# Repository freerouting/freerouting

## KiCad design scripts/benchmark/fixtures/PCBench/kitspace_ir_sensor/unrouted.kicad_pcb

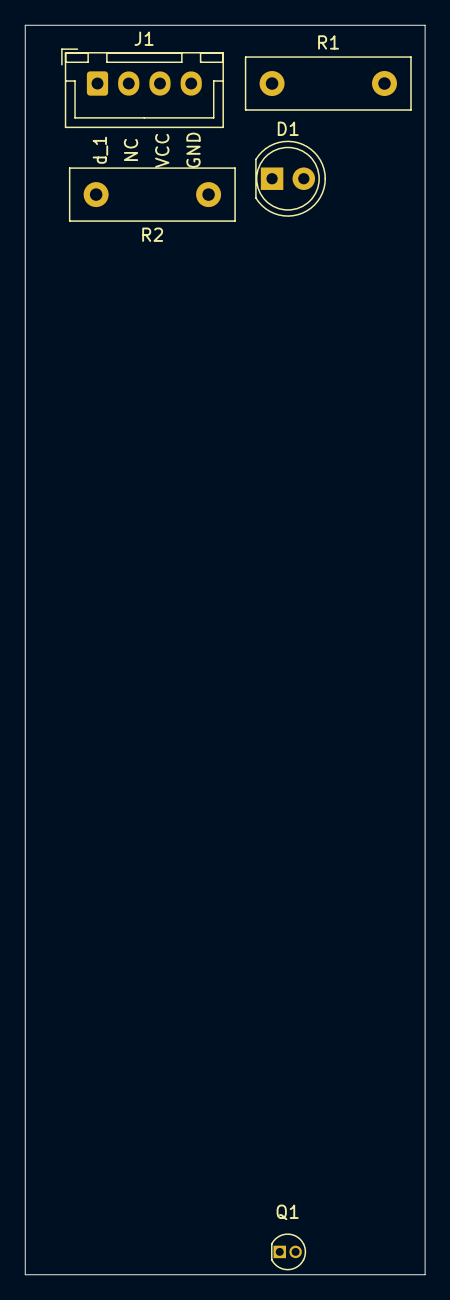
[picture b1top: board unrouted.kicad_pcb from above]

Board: 2 copper layers, 32.0 x 100.0 mm, 5 parts (0 on the bottom side), 4 nets, no tracks yet.

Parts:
D1: LED; LED_D5.0mm
J1: Conn_01x04; JST_XH_B4B-XH-A_1x04_P2.50mm_Vertical
Q1: Q_Photo_NPN; OP505A
R1: 47; R_Box_L13.0mm_W4.0mm_P9.00mm
R2: 10k; R_Box_L13.0mm_W4.0mm_P9.00mm

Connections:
+5V: J1.3, R1.1, R2.1
GND: D1.1, J1.4, Q1.2
unnamed: D1.2, R1.2
data: J1.1, Q1.1, R2.2

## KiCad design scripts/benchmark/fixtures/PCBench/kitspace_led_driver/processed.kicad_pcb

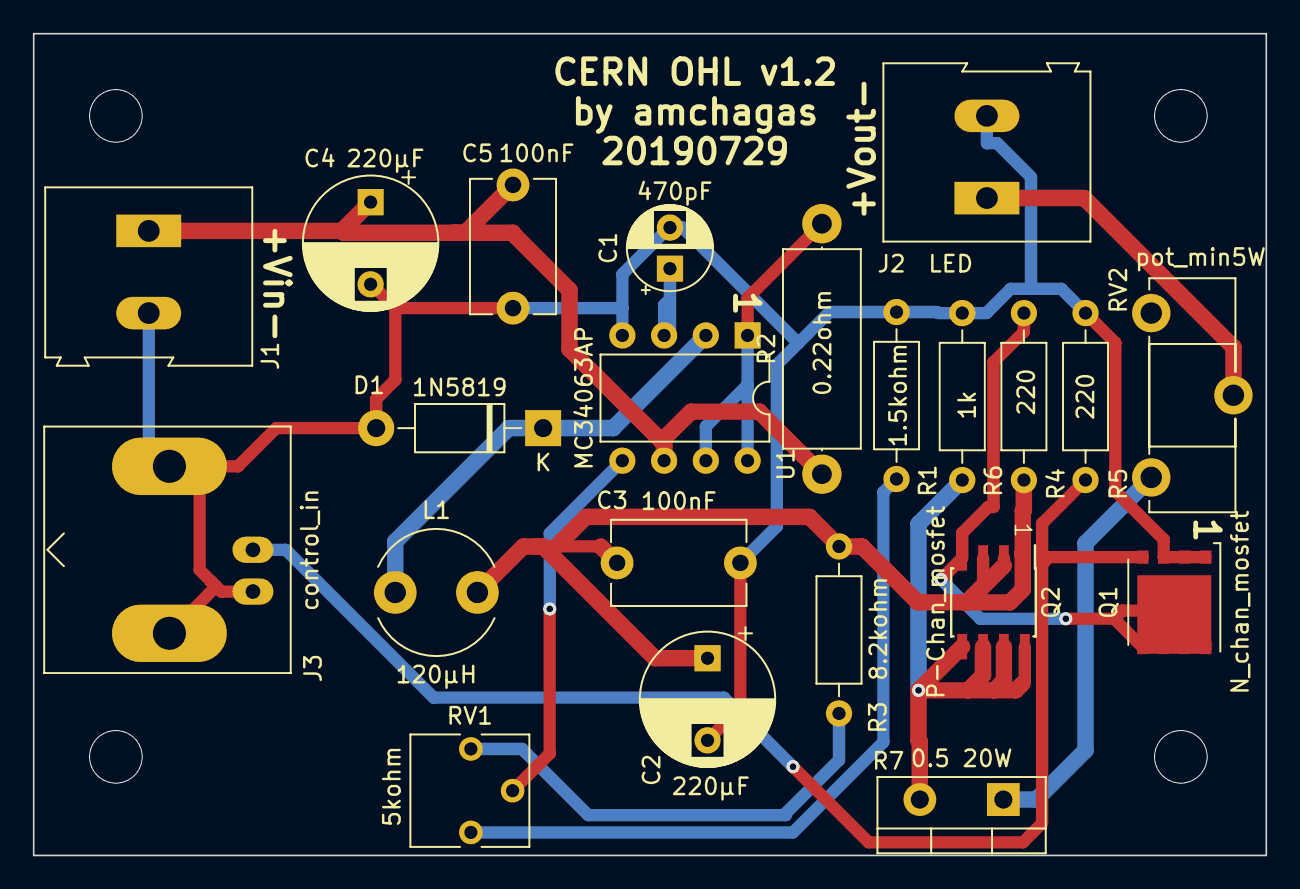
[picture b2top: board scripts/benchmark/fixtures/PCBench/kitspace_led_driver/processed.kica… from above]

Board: 2 copper layers, 75.0 x 50.0 mm, 26 parts (0 on the bottom side), 14 nets.

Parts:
C1: 470pF; CP_Radial_D5.0mm_P2.50mm
C2, C4: 220µF; CP_Radial_D8.0mm_P5.00mm
C3, C5: 100nF; C_Disc_D8.0mm_W5.0mm_P7.50mm
D1: 1N5819; D_DO-41_SOD81_P10.16mm_Horizontal
H1, H2, H3, H4: MountingHole; MountingHole_3.2mm_M3
J1: Vin; TerminalBlock_Altech_AK300-2_P5.00mm
J2: LED; TerminalBlock_Altech_AK300-2_P5.00mm
J3: control_in; BNC_Amphenol_B6252HB-NPP3G-50_Horizontal
L1: 120µH; L_Radial_D7.5mm_P5.00mm_Fastron_07P
Q1: N_chan_mosfet; TDSON-8-1
Q2: P-Chan_mosfet; SOIC-8_3.9x4.9mm_P1.27mm
R1: 1.5kohm; R_Axial_DIN0207_L6.3mm_D2.5mm_P10.16mm_Horizontal
R2: 0.22ohm; R_Axial_DIN0414_L11.9mm_D4.5mm_P15.24mm_Horizontal
R3: 8.2kohm; R_Axial_DIN0207_L6.3mm_D2.5mm_P10.16mm_Horizontal
R4, R5: 220; R_Axial_DIN0207_L6.3mm_D2.5mm_P10.16mm_Horizontal
R6: 1k; R_Axial_DIN0207_L6.3mm_D2.5mm_P10.16mm_Horizontal
R7: 0.5 20W; TO-220-2_Vertical
RV1: 5kohm; Potentiometer_Vishay_T73YP_Vertical
RV2: pot_min5W; Potentiometer_ACP_CA14-H5_Horizontal
U1: MC34063AP; DIP-8_W7.62mm

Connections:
GND: C1.2, C2.2, C3.1, C4.2, C5.2, D1.2, J1.2, J2.2, J3.2, Q1.1, Q1.2, Q1.3, R1.2, R5.1, R6.2, U1.4
unnamed: C1.1, U1.3
unnamed: C2.1, C3.2, L1.2, Q2.1, Q2.2, Q2.3, R3.1, R4.2
unnamed: D1.1, L1.1, U1.2
unnamed: J2.1, RV2.2
unnamed: J3.1, Q1.4, R5.2
unnamed: Q1.5, Q2.4, R4.1
unnamed: Q2.5, Q2.6, Q2.7, Q2.8, R6.1, R7.2
unnamed: R1.1, RV1.1
unnamed: R2.2, U1.1, U1.7, U1.8
unnamed: R3.2, RV1.3
unnamed: R7.1, RV2.3
unnamed: RV1.2, U1.5
VDD: C4.1, C5.1, J1.1, R2.1, U1.6

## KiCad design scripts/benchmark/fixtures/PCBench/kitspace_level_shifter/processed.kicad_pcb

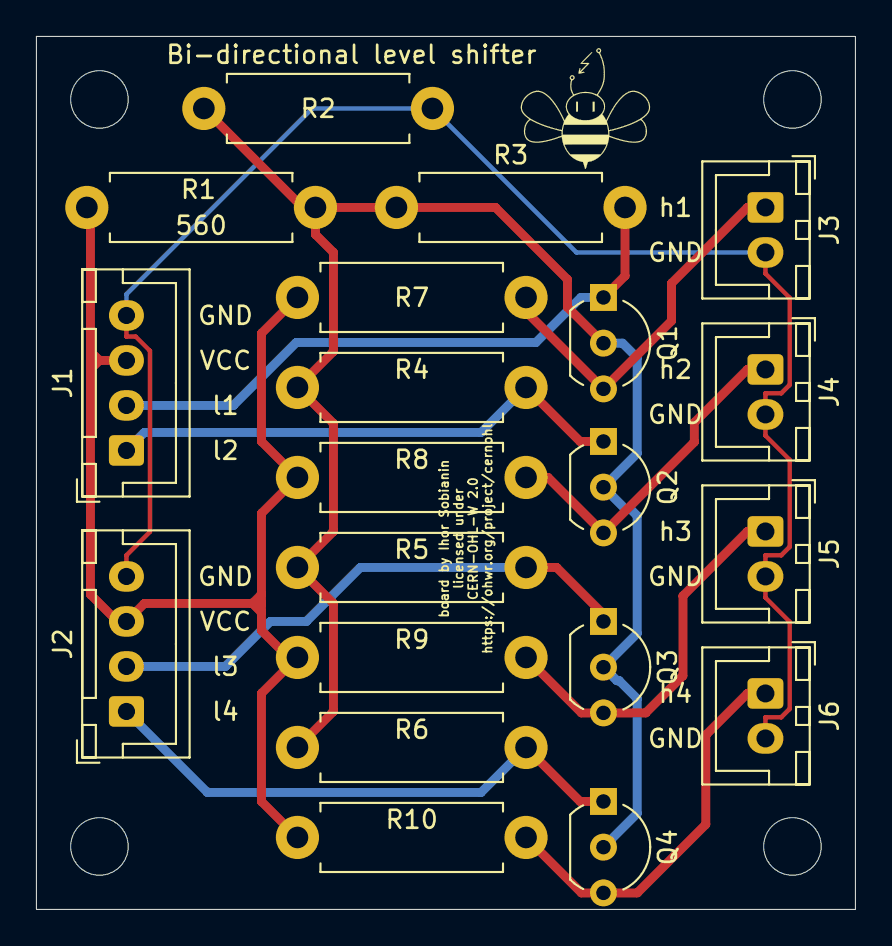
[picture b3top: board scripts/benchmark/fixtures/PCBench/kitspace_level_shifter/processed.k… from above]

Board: 2 copper layers, 45.5 x 48.5 mm, 20 parts (0 on the bottom side), 11 nets.

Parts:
J1, J2: Conn_01x04; JST_XH_B4B-XH-A_1x04_P2.50mm_Vertical
J3, J4, J5, J6: Conn_01x02; JST_XH_B2B-XH-A_1x02_P2.50mm_Vertical
Q1, Q2, Q3, Q4: 2N7000; TO-92_Inline_Wide
R1: 560; R_Axial_DIN0411_L9.9mm_D3.6mm_P12.70mm_Horizontal
R2, R3, R4, R5, R6, R7, R8, R9, R10: 1k; R_Axial_DIN0411_L9.9mm_D3.6mm_P12.70mm_Horizontal

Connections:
+3V3: Q1.2, Q2.2, Q3.2, Q4.2, R1.1, R2.2, R3.1, R4.1, R5.1, R6.1
+5V: J1.3, J2.3, R1.2, R7.1, R8.1, R9.1, R10.1
GND: J1.4, J2.4, J3.2, J4.2, J5.2, J6.2, R2.1
d1_h: J3.1, Q1.3, R7.2
d1_l: J1.2, Q1.1, R3.2
d2_h: J4.1, Q2.3, R8.2
d2_l: J1.1, Q2.1, R4.2
d3_h: J5.1, Q3.3, R9.2
d3_l: J2.2, Q3.1, R5.2
d4_h: J6.1, Q4.3, R10.2
d4_l: J2.1, Q4.1, R6.2

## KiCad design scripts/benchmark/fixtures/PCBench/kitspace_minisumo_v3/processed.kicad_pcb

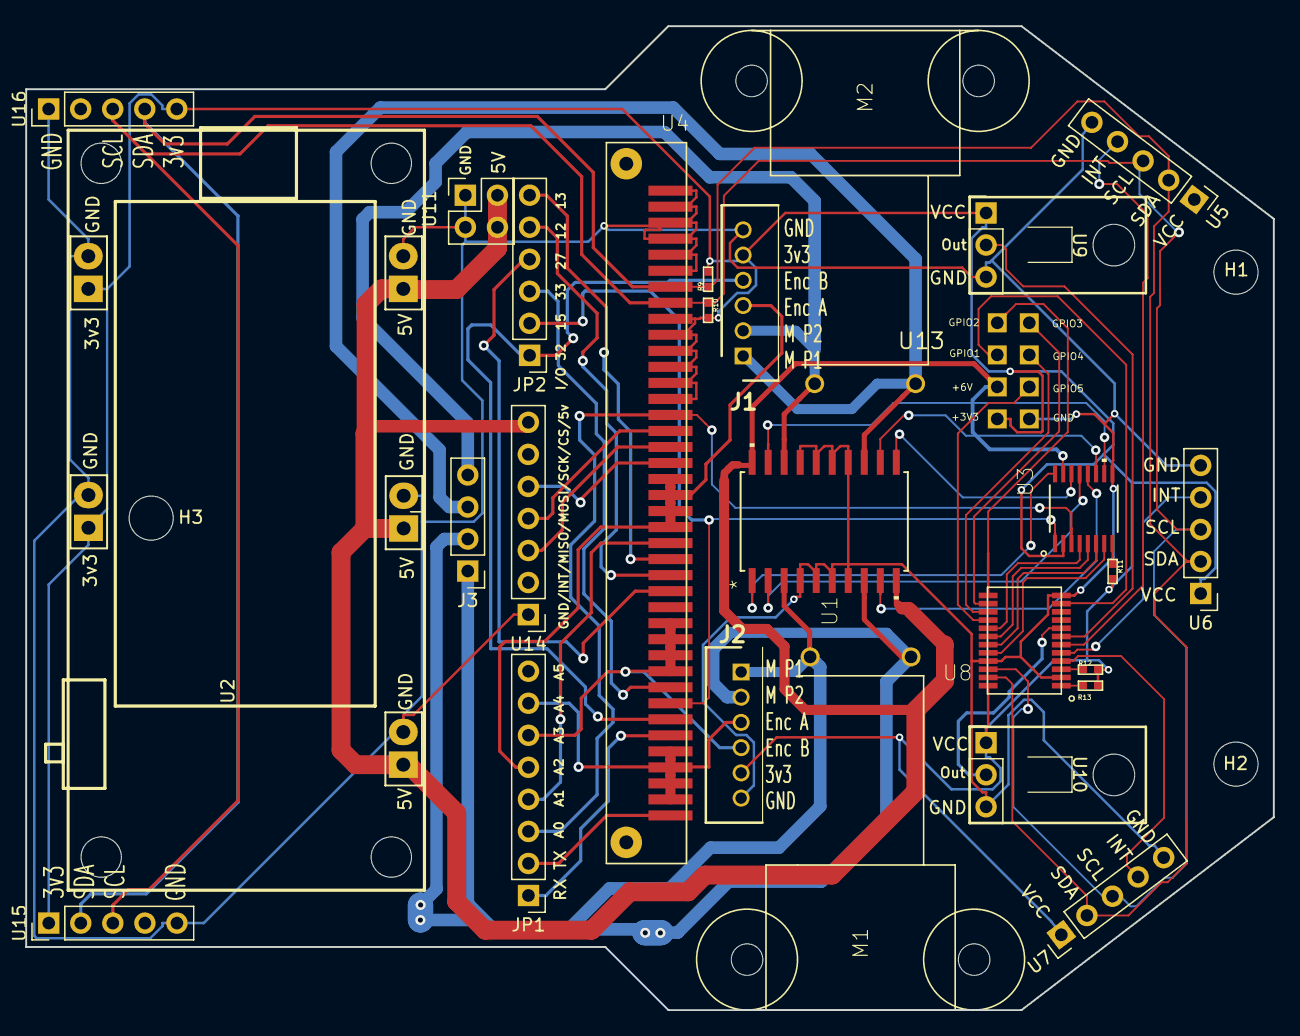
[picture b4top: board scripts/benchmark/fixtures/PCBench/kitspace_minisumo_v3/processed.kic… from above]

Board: 2 copper layers, 98.9 x 78.0 mm, 30 parts (0 on the bottom side), 48 nets.

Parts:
H1, H2, H3: MountingHole; MountingHole_3.5mm
J1: Right Motor; SHDR6W50P0X200_1X6_1390X450X600P
J2: Left Motor; SHDR6W50P0X200_1X6_1390X450X600P
J3: Motor Connector2; PinHeader_1x04_P2.54mm_Vertical
JP1: Conn_01x08; PinHeader_1x08_P2.54mm_Vertical
JP2: Conn_01x06; PinHeader_1x06_P2.54mm_Vertical
M1, M2: N20_MOTOR; N20-MOTOR-BRACKET
R9, R10, R11, R12, R13: 10k; RES_0402
U1: L293DD; SO-20
U2: 16340_Battery_Module; 16340 Battery Module
U3: TXB0106PWRPW16-L; PW16-L
U4: BBC Micro:bit; CYCLONE_MICROBIT_VERTICAL
U5: VL53L1X Right; PinHeader_1x05_P2.54mm_Vertical
U6: VL53L1X Center; PinHeader_1x05_P2.54mm_Vertical
U7: VL53L1X Left; PinHeader_1x05_P2.54mm_Vertical
U8: TCA9539PWR; 24-TSSOP
U9: NW; SparkFun QRE1113
U10: NE; SparkFun QRE1113
U11: Conn_02x02_Top_Bottom; PinHeader_2x02_P2.54mm_Vertical
U13: SUMO_IO
U14: Conn_01x07; PinHeader_1x07_P2.54mm_Vertical
U15, U16: Conn_01x05_2; PinHeader_1x05_P2.54mm_Vertical

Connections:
+3V3: J1.5, J2.5, R9.P$2, R10.P$2, R11.P$2, R12.P$2, R13.P$2, U2.3, U3.2, U4.3.3V@9, U4.3.3V@10, U4.3.3V@11, U4.3.3V@12, U4.3.3V@13, U4.3.3V@14, U6.1, U7.1, U8.24, U9.+3V3, U10.+3V3, U13.3V3, U15.1, U16.5
+5V: U1.10, U1.20, U2.1, U3.15, U11.2, U11.4, U13.6V, U14.7
/INPUT_1: U3.4, U8.17
/INPUT_2: U3.5, U8.18
/INPUT_3: U3.6, U8.19
/INPUT_4: U3.7, U8.20
/IO1: U8.11, U13.GPIO1
/IO2: U8.13, U13.GPIO2
/IO3: U8.14, U13.GPIO3
/IO4: U8.15, U13.GPIO4
/IO5: U8.16, U13.GPIO5
/ML1: J2.1, J3.1, M1.1, U1.3
/ML2: J2.2, J3.2, M1.2, U1.8
/MR1: J1.1, J3.3, M2.1, U1.13
/MR2: J1.2, J3.4, M2.2, U1.18
/NE: U8.8, U10.SIGNAL
/NW: U8.7, U9.SIGNAL
/XS1: U7.4, U8.4
/XS2: U6.4, U8.5
/XS3: U5.4, U8.6
A0: JP1.3, U3.3, U4.P16
A1: JP1.4, U4.RESERVED
A2: J1.3, JP1.5, U4.P2_ANALOG_IN@19, U4.P2_ANALOG_IN@20, U4.P2_ANALOG_IN@21, U4.P2_ANALOG_IN@22
A3: J2.4, JP1.6, U4.P1_ANALOG_IN@28, U4.P1_ANALOG_IN@29, U4.P1_ANALOG_IN@30, U4.P1_ANALOG_IN@31
A4: J2.3, JP1.7, U4.P0_ANALOG_IN@36, U4.P0_ANALOG_IN@37, U4.P0_ANALOG_IN@38, U4.P0_ANALOG_IN@39
GND: J1.6, J2.6, U1.4, U1.5, U1.6, U1.7, U1.14, U1.15, U1.16, U1.17, U2.2, U2.4, U3.9, U4.GND@1, U4.GND@2, U4.GND@3, U4.GND@4, U4.GND@5, U4.GND@6, U5.5, U6.5, U7.5, U8.2, U8.12, U8.21, U9.GND, U10.GND, U11.1, U11.3, U13.GND, U14.1, U15.5, U16.1
IO12: JP2.5, U4.P10_LED_COL_3_ANALO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
IO13: JP2.6, U4.P11_BUTTON_B
IO15: JP2.2, U3.1, U4.P6_LED_COL_9
IO16: JP1.1, U4.P4_LED_COL_2_ANALOG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
IO17: JP1.2, U4.P3_LED_COL_1_ANALOG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
IO27: JP2.4, U4.P9_LED_COL_7
IO32: J1.4, JP2.1, U4.P5_BUTTON_A
IO33: JP2.3, U4.P7_LED_COL8
MISO: U4.P14_MISO, U14.3
MOSI: U4.P15_MOSI, U14.4
unnamed: R11.P$1, U3.8
unnamed: R12.P$1, U8.3
unnamed: R13.P$1, U8.1
unnamed: U1.1, U3.16
unnamed: U1.2, U3.13
unnamed: U1.9, U3.12
unnamed: U1.11, U3.14
unnamed: U1.12, U3.11
unnamed: U1.19, U3.10
SCK: U4.P13_SCK, U14.5
SCL: R10.P$1, U4.P21_SCL, U5.3, U6.3, U7.3, U8.22, U15.3, U16.3
SDA: R9.P$1, U4.P20_SDA, U5.2, U6.2, U7.2, U8.23, U15.2, U16.4

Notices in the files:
scripts/benchmark/fixtures/PCBench/kitspace_led_driver/processed.kicad_pcb:
CERN OHL v1.2
scripts/benchmark/fixtures/PCBench/kitspace_level_shifter/processed.kicad_pcb:
licensed under
CERN-OHL-W 2.0
scripts/benchmark/fixtures/PCBench/kitspace_minisumo_v3/processed.kicad_pcb:
CERN-OHl-P
